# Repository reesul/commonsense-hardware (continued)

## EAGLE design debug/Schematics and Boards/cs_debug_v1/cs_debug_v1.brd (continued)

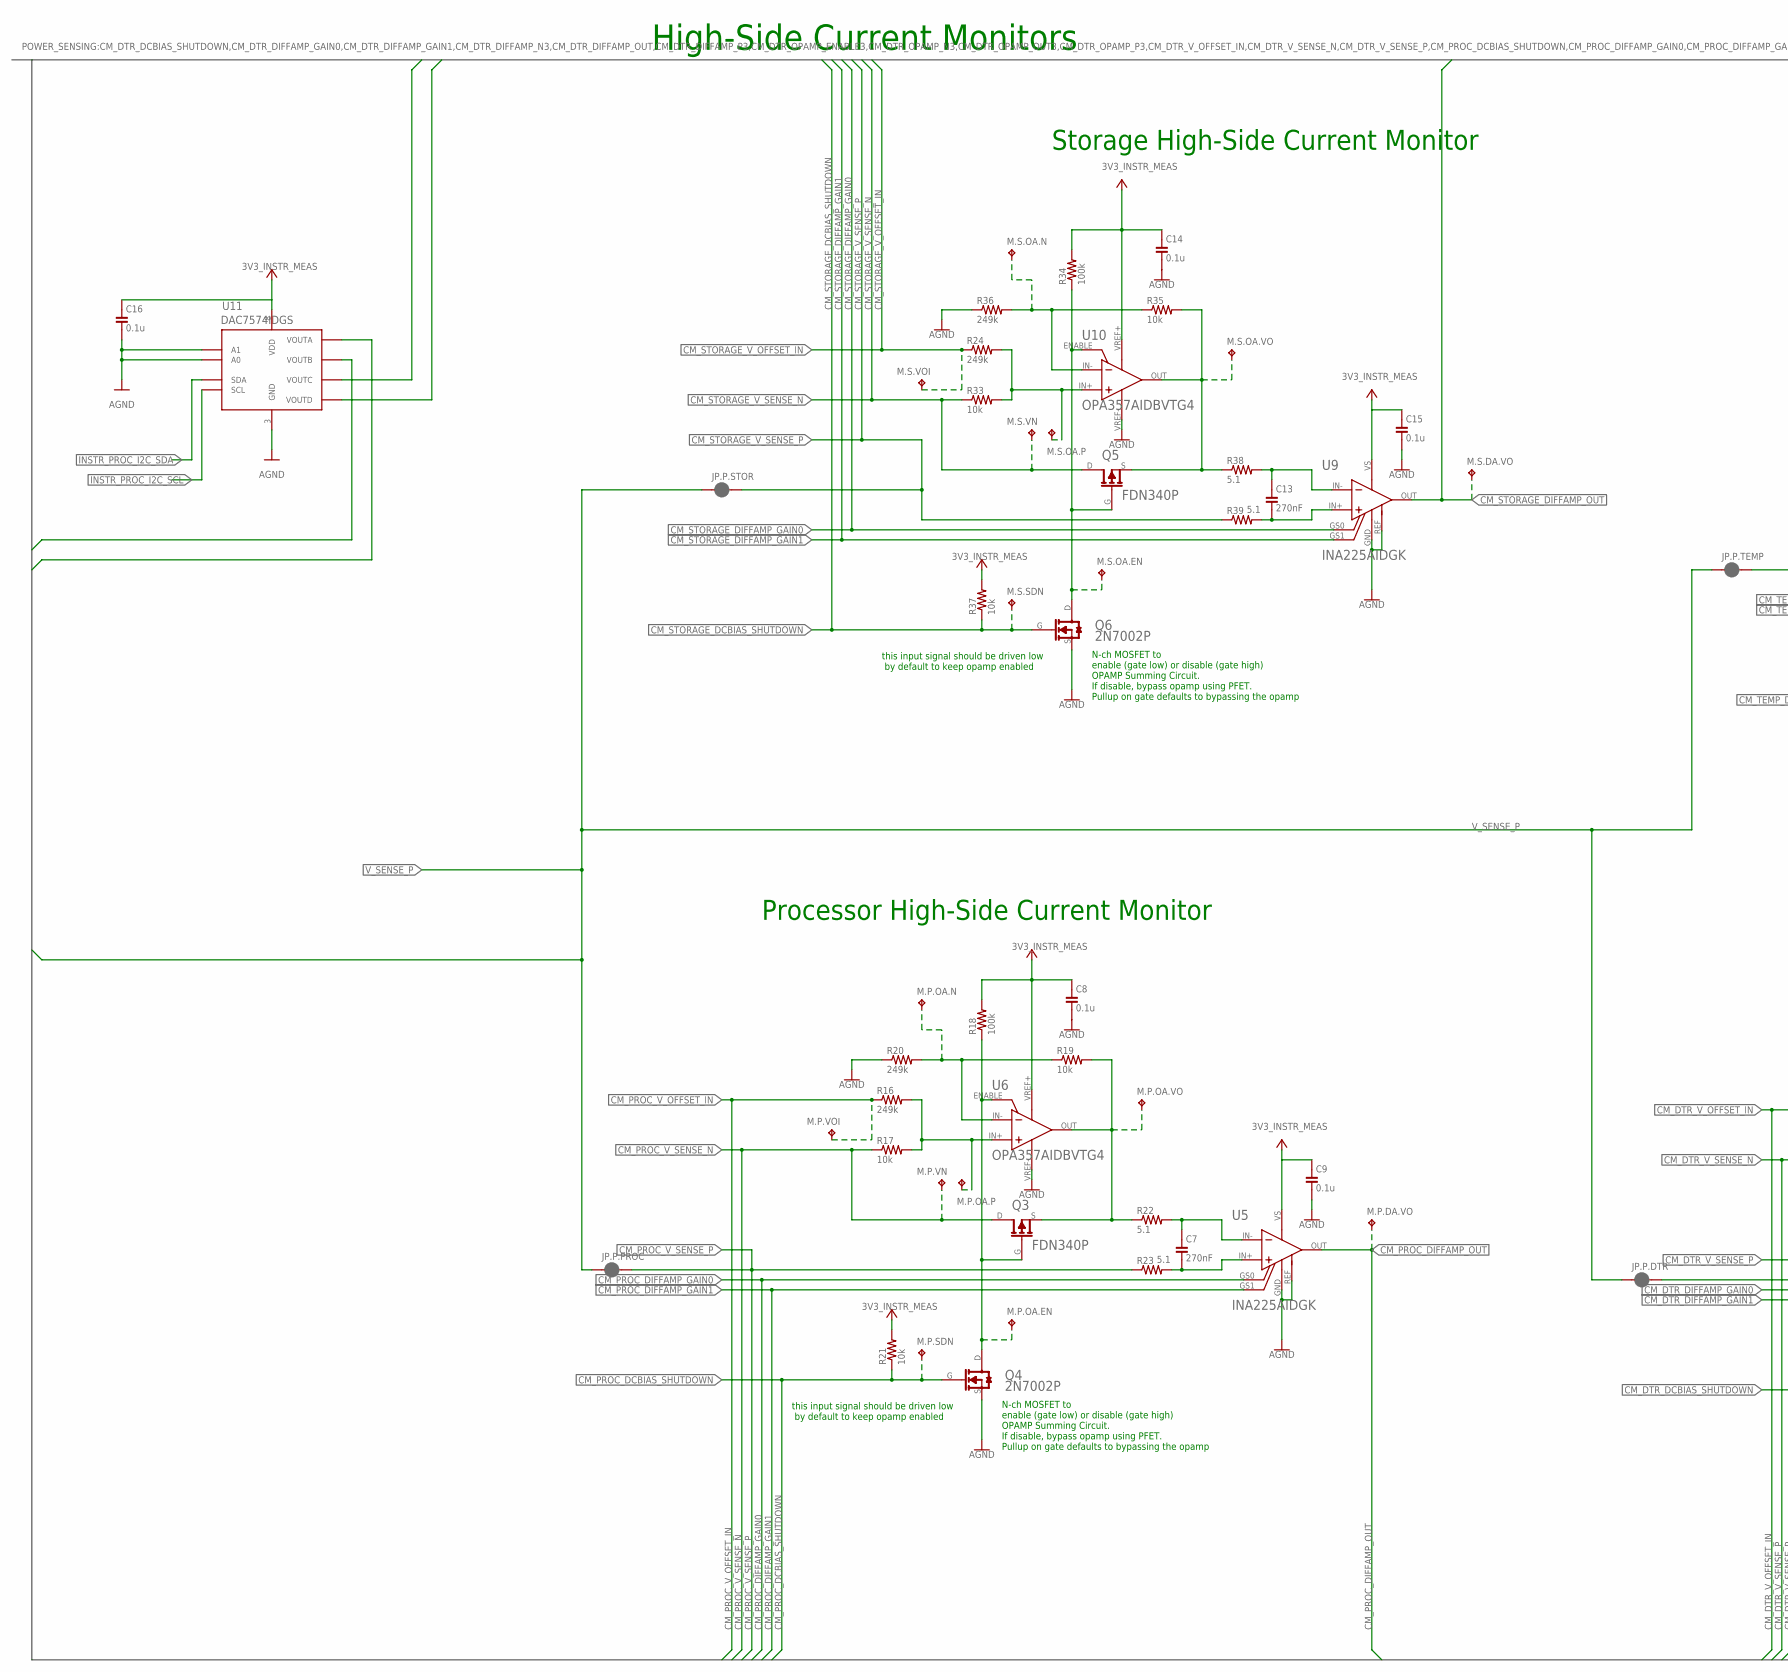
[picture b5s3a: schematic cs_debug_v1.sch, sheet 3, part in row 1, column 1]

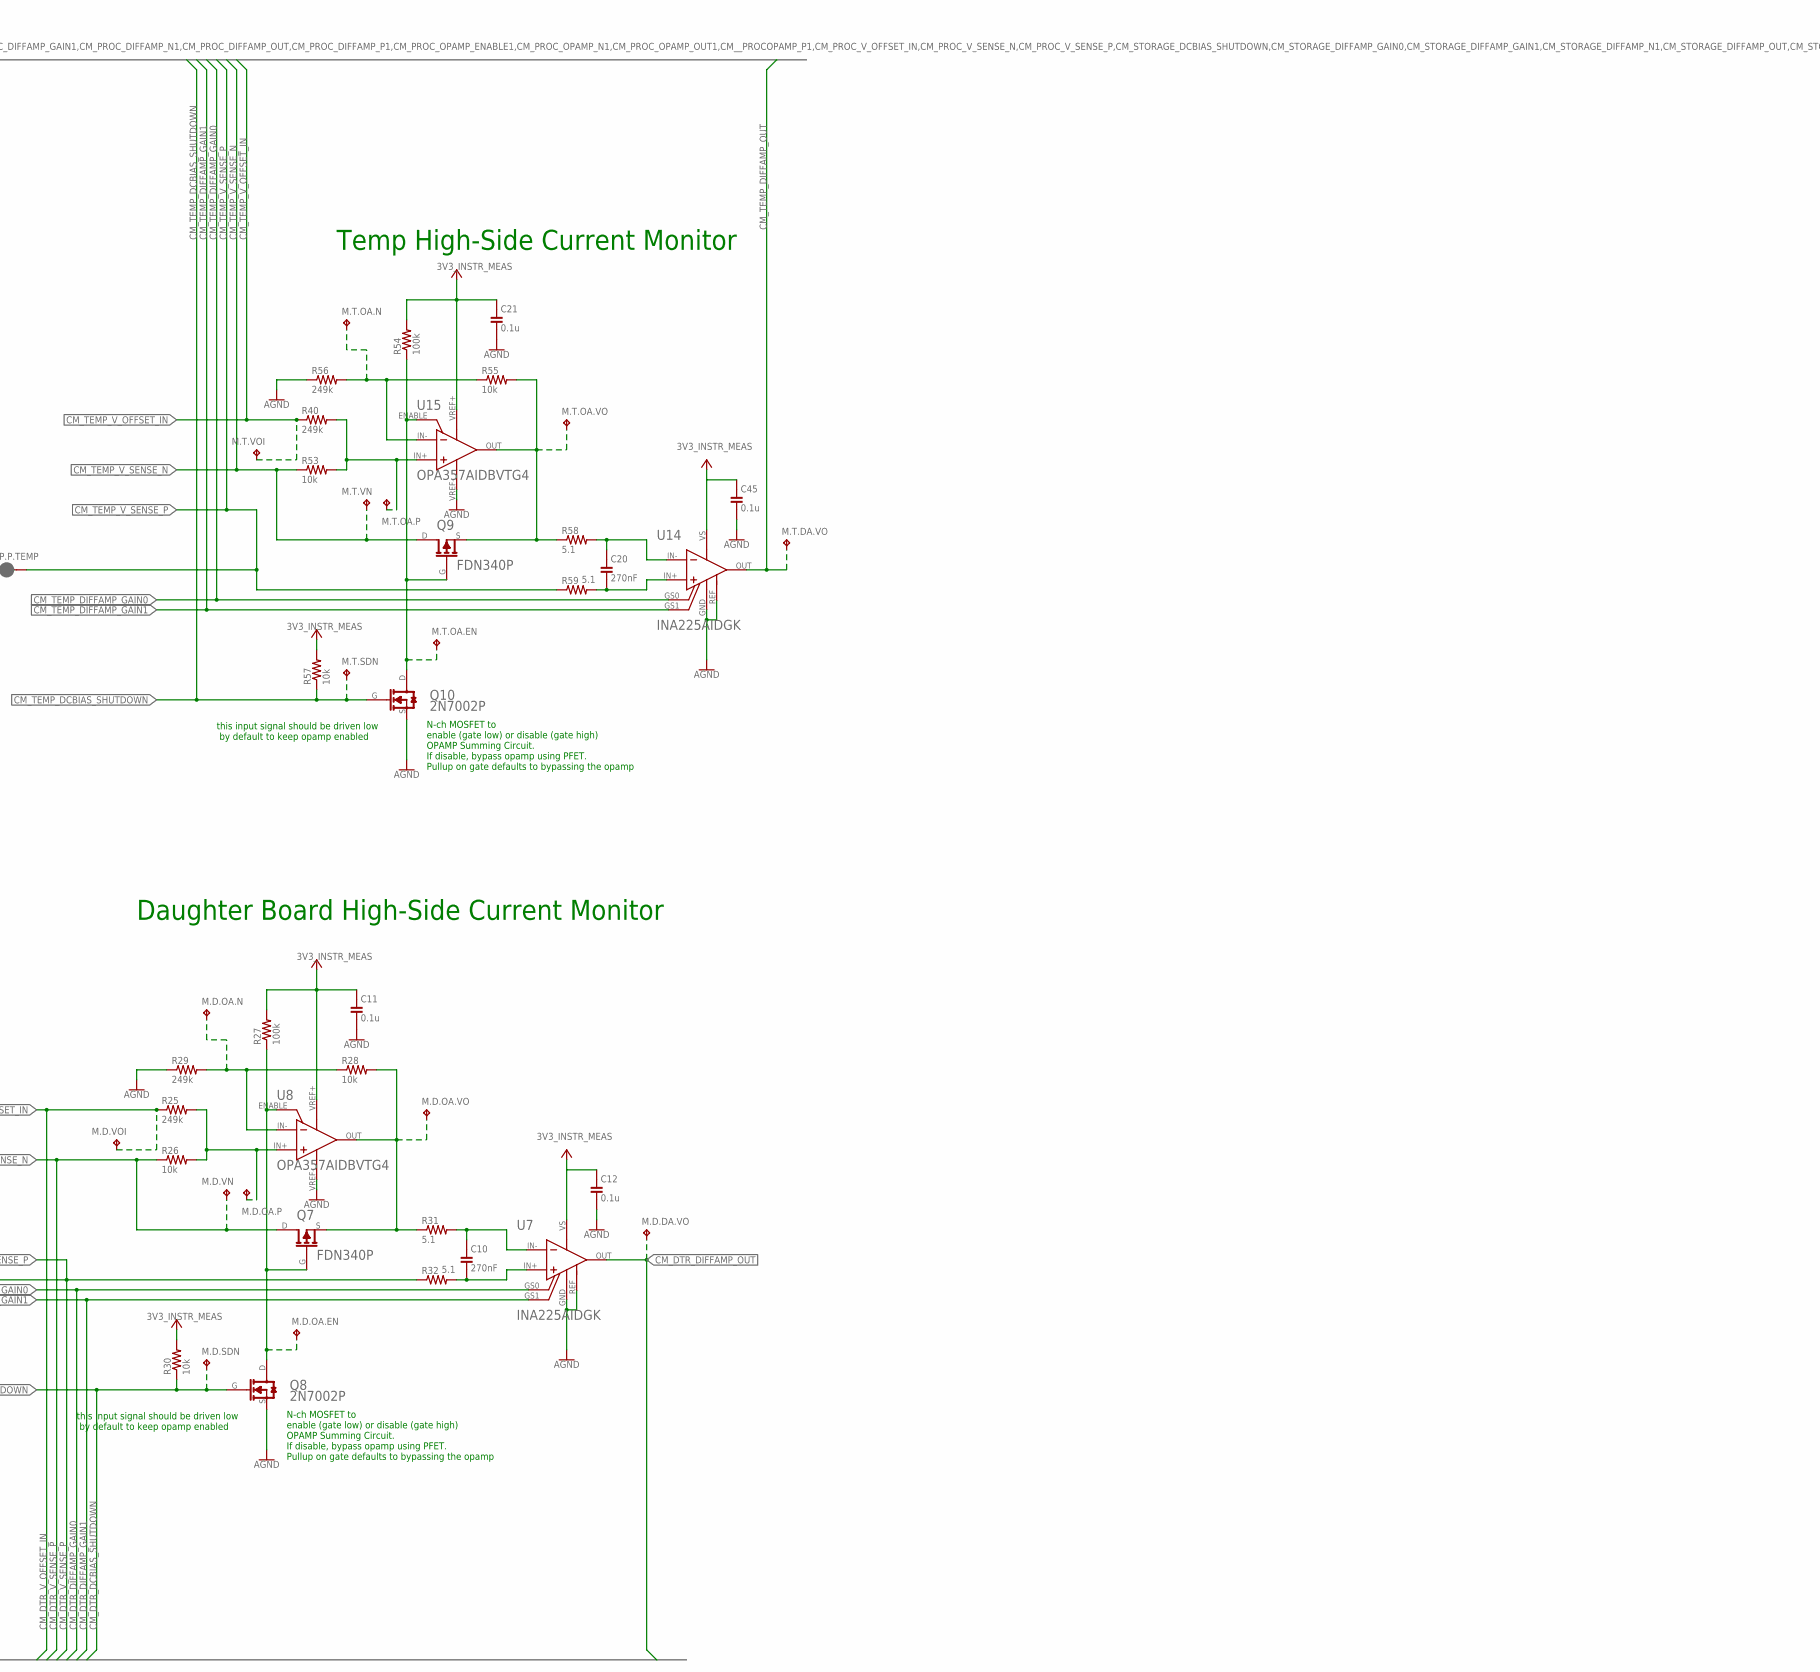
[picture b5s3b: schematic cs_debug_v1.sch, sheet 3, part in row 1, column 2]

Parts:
C7, C10, C13, C20: 270nF; C0603; VOLTAGE 10V; MPN C0603C274K8PACTU
C8, C9, C11, C12, C14, C15, C16, C21, C45: 0.1u; C0402; VOLTAGE 10V; MPN C0402C104K8RACTU
JP.P.DTR, JP.P.PROC, JP.P.STOR, JP.P.TEMP: JUMPER-SMT_2_NC_PASTE_NO-SILK; SMT-JUMPER_2_NC_PASTE_NO-SILK
M.D.DA.VO, M.D.OA.EN, M.D.OA.N, M.D.OA.P, M.D.OA.VO, M.D.SDN, M.D.VN, M.D.VOI, M.P.DA.VO, M.P.OA.EN, M.P.OA.N, M.P.OA.P, M.P.OA.VO, M.P.SDN, M.P.VN, M.P.VOI, M.S.DA.VO, M.S.OA.EN, M.S.OA.N, M.S.OA.P, M.S.OA.VO, M.S.SDN, M.S.VN, M.S.VOI, M.T.DA.VO, M.T.OA.EN, M.T.OA.N, M.T.OA.P, M.T.OA.VO, M.T.SDN, M.T.VN, M.T.VOI: TPTP10SQ; TP10SQ
Q3, Q5, Q7, Q9: FDN340P; SOT23-3_FDN340P; PART_NO FDN340P
Q4, Q6, Q8, Q10: 2N7002P; SOT23-3_2N7002P; PART_NO 2N7002P
R16, R20, R24, R25, R29, R36, R40, R56: 249k; R0402; MPN ERA-2AEB2491X
R17, R19, R26, R28, R33, R35, R53, R55: 10k; R0402; MPN ERA-2AEB103X
R18, R27, R34, R54: 100k; R0402; MPN ERJ-2RKF1003X
R21, R30, R37, R57: 10k; R0402; MPN ERJ-2RKF1002X
R22, R23, R31, R32, R38, R39, R58, R59: 5.1; R0603; MPN ERJ-3BQF5R1V
U5, U7, U9, U14: INA225AIDGK; DGK-MSOP8_INA225; MPN INA225AIDGKT
U6, U8, U10, U15: OPA357AIDBVTG4; PART_NO OPA357AIDBVTG4
U11: DAC7574IDGS; DGS10; MPN DAC7574IDGS

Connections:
3V3_INSTR_MEAS: C8.1, C9.1, C11.1, C12.1, C14.1, C15.1, C16.1, C21.1, C45.1, R18.2, R21.2, R27.2, R30.2, R34.2, R37.2, R54.2, R57.2, U5.VS (V+), U6.VREF+ (V+), U7.VS (V+), U8.VREF+ (V+), U9.VS (V+), U10.VREF+ (V+), U11.8 (VDD), U14.VS (V+), U15.VREF+ (V+); also elsewhere on the board
AGND: C8.2, C9.2, C11.2, C12.2, C14.2, C15.2, C16.2, C21.2, C45.2, Q4.S (SOURCE), Q6.S (SOURCE), Q8.S (SOURCE), Q10.S (SOURCE), R20.1, R29.1, R36.1, R56.1, U5.GND (V-), U5.REF, U6.VREF- (V-), U7.GND (V-), U7.REF, U8.VREF- (V-), U9.GND (V-), U9.REF, U10.VREF- (V-), U11.3 (GND), U11.9 (A0), U11.10 (A1), U14.GND (V-), U14.REF, U15.VREF- (V-); also elsewhere on the board
CM_DIFFAMP_N1: C20.1, R58.2, U14.IN-
CM_DIFFAMP_N2: C13.1, R38.2, U9.IN-
CM_DIFFAMP_N3: C10.1, R31.2, U7.IN-
CM_DIFFAMP_N4: C7.1, R22.2, U5.IN-
CM_DIFFAMP_P1: C20.2, R59.2, U14.IN+
CM_DIFFAMP_P2: C13.2, R39.2, U9.IN+
CM_DIFFAMP_P3: C10.2, R32.2, U7.IN+
CM_DIFFAMP_P4: C7.2, R23.2, U5.IN+
CM_DTR_DCBIAS_SHUTDOWN: M.D.SDN.TP, Q8.G (GATE), R30.1; also elsewhere on the board
CM_DTR_DIFFAMP_GAIN0: U7.GS0; also elsewhere on the board
CM_DTR_DIFFAMP_GAIN1: U7.GS1; also elsewhere on the board
CM_DTR_DIFFAMP_OUT: M.D.DA.VO.TP, U7.OUT; also elsewhere on the board
CM_DTR_V_OFFSET_IN: M.D.VOI.TP, R25.1, U11.2 (VOUTB)
CM_DTR_V_SENSE_N: M.D.VN.TP, Q7.D, R26.1; also elsewhere on the board
CM_DTR_V_SENSE_P: JP.P.DTR.2, R32.1
CM_OPAMP_ENABLE1: M.T.OA.EN.TP, Q9.G, Q10.D (DRAIN), R54.1, U15.ENABLE
CM_OPAMP_ENABLE2: M.S.OA.EN.TP, Q5.G, Q6.D (DRAIN), R34.1, U10.ENABLE
CM_OPAMP_ENABLE3: M.D.OA.EN.TP, Q7.G, Q8.D (DRAIN), R27.1, U8.ENABLE
CM_OPAMP_ENABLE4: M.P.OA.EN.TP, Q3.G, Q4.D (DRAIN), R18.1, U6.ENABLE
CM_OPAMP_N1: M.T.OA.N.TP, R55.1, R56.2, U15.IN-
CM_OPAMP_N2: M.S.OA.N.TP, R35.1, R36.2, U10.IN-
CM_OPAMP_N3: M.D.OA.N.TP, R28.1, R29.2, U8.IN-
CM_OPAMP_N4: M.P.OA.N.TP, R19.1, R20.2, U6.IN-
CM_OPAMP_OUT1: M.T.OA.VO.TP, Q9.S, R55.2, R58.1, U15.OUT
CM_OPAMP_OUT2: M.S.OA.VO.TP, Q5.S, R35.2, R38.1, U10.OUT
CM_OPAMP_OUT3: M.D.OA.VO.TP, Q7.S, R28.2, R31.1, U8.OUT
CM_OPAMP_OUT4: M.P.OA.VO.TP, Q3.S, R19.2, R22.1, U6.OUT
CM_OPAMP_P1: M.T.OA.P.TP, R40.2, R53.2, U15.IN+
CM_OPAMP_P2: M.S.OA.P.TP, R24.2, R33.2, U10.IN+
CM_OPAMP_P3: M.D.OA.P.TP, R25.2, R26.2, U8.IN+
CM_OPAMP_P4: M.P.OA.P.TP, R16.2, R17.2, U6.IN+
CM_PROC_DCBIAS_SHUTDOWN: M.P.SDN.TP, Q4.G (GATE), R21.1; also elsewhere on the board
CM_PROC_DIFFAMP_GAIN0: U5.GS0; also elsewhere on the board
CM_PROC_DIFFAMP_GAIN1: U5.GS1; also elsewhere on the board
CM_PROC_DIFFAMP_OUT: M.P.DA.VO.TP, U5.OUT; also elsewhere on the board
CM_PROC_V_OFFSET_IN: M.P.VOI.TP, R16.1, U11.1 (VOUTA)
CM_PROC_V_SENSE_N: M.P.VN.TP, Q3.D, R17.1; also elsewhere on the board
CM_PROC_V_SENSE_P: JP.P.PROC.2, R23.1
CM_STORAGE_DCBIAS_SHUTDOWN: M.S.SDN.TP, Q6.G (GATE), R37.1; also elsewhere on the board
CM_STORAGE_DIFFAMP_GAIN0: U9.GS0; also elsewhere on the board
CM_STORAGE_DIFFAMP_GAIN1: U9.GS1; also elsewhere on the board
CM_STORAGE_DIFFAMP_OUT: M.S.DA.VO.TP, U9.OUT; also elsewhere on the board
CM_STORAGE_V_OFFSET_IN: M.S.VOI.TP, R24.1, U11.4 (VOUTC)
CM_STORAGE_V_SENSE_N: M.S.VN.TP, Q5.D, R33.1; also elsewhere on the board
CM_STORAGE_V_SENSE_P: JP.P.STOR.2, R39.1
CM_TEMP_DCBIAS_SHUTDOWN: M.T.SDN.TP, Q10.G (GATE), R57.1; also elsewhere on the board
CM_TEMP_DIFFAMP_GAIN0: U14.GS0; also elsewhere on the board
CM_TEMP_DIFFAMP_GAIN1: U14.GS1; also elsewhere on the board
CM_TEMP_DIFFAMP_OUT: M.T.DA.VO.TP, U14.OUT; also elsewhere on the board
CM_TEMP_V_OFFSET_IN: M.T.VOI.TP, R40.1, U11.5 (VOUTD)
CM_TEMP_V_SENSE_N: M.T.VN.TP, Q9.D, R53.1; also elsewhere on the board
CM_TEMP_V_SENSE_P: JP.P.TEMP.2, R59.1
INSTR_PROC_I2C_SCL: U11.6 (SCL); also elsewhere on the board
INSTR_PROC_I2C_SDA: U11.7 (SDA); also elsewhere on the board
V_SENSE_P: JP.P.DTR.1, JP.P.PROC.1, JP.P.STOR.1, JP.P.TEMP.1; also elsewhere on the board

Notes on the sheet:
High-Side Current Monitors
Temp High-Side Current Monitor
this input signal should be driven low by default to keep opamp enabled
N-ch MOSFET to enable (gate low) or disable (gate high) OPAMP Summing Circuit. If disable, bypass opamp using PFET. Pullup on gate defaults to bypassing the opamp
Storage High-Side Current Monitor
Daughter Board High-Side Current Monitor
Processor High-Side Current Monitor

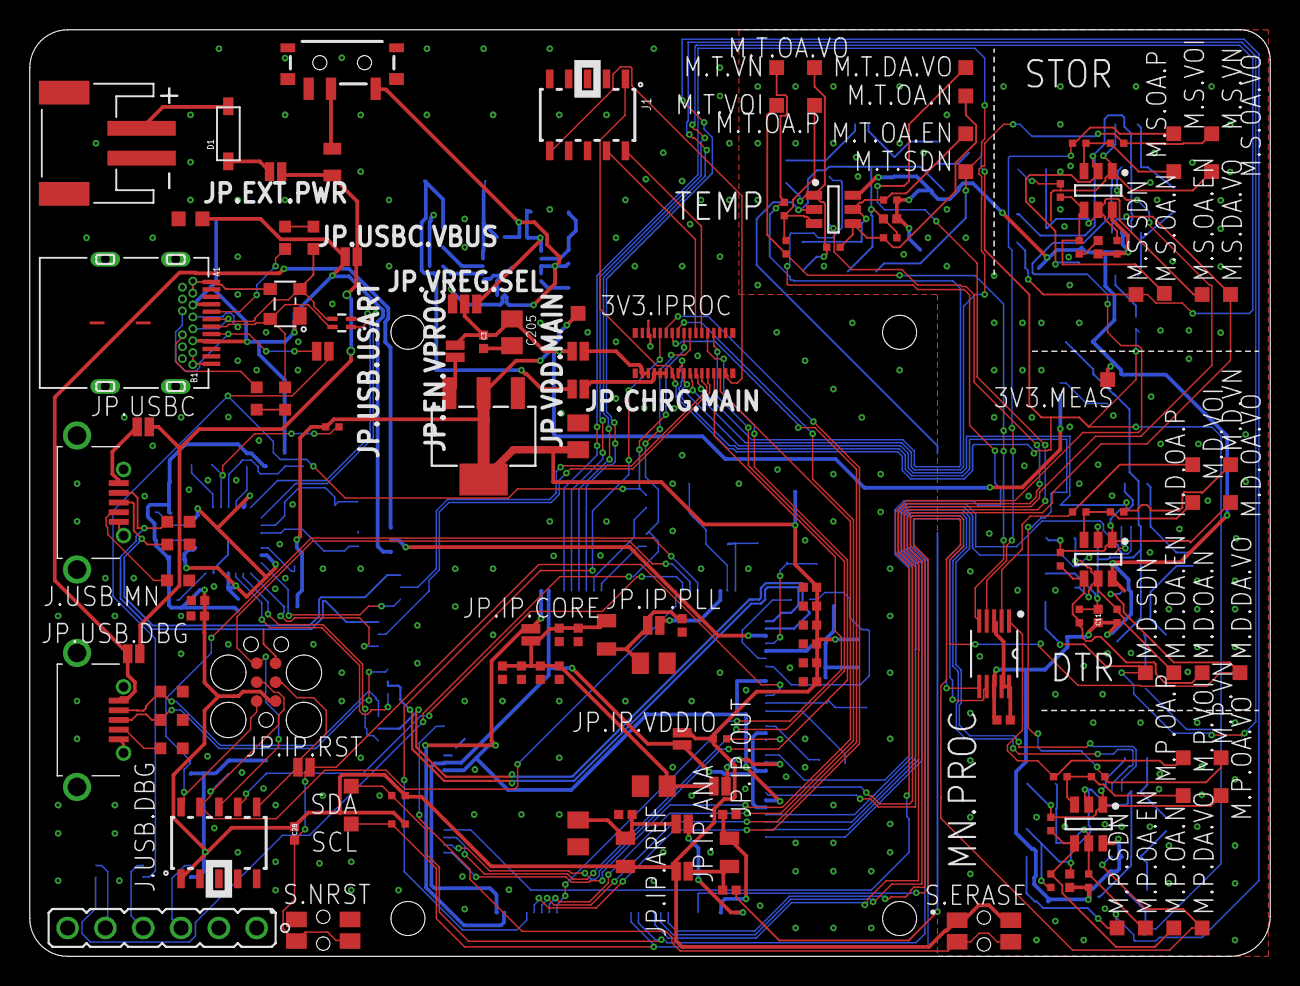
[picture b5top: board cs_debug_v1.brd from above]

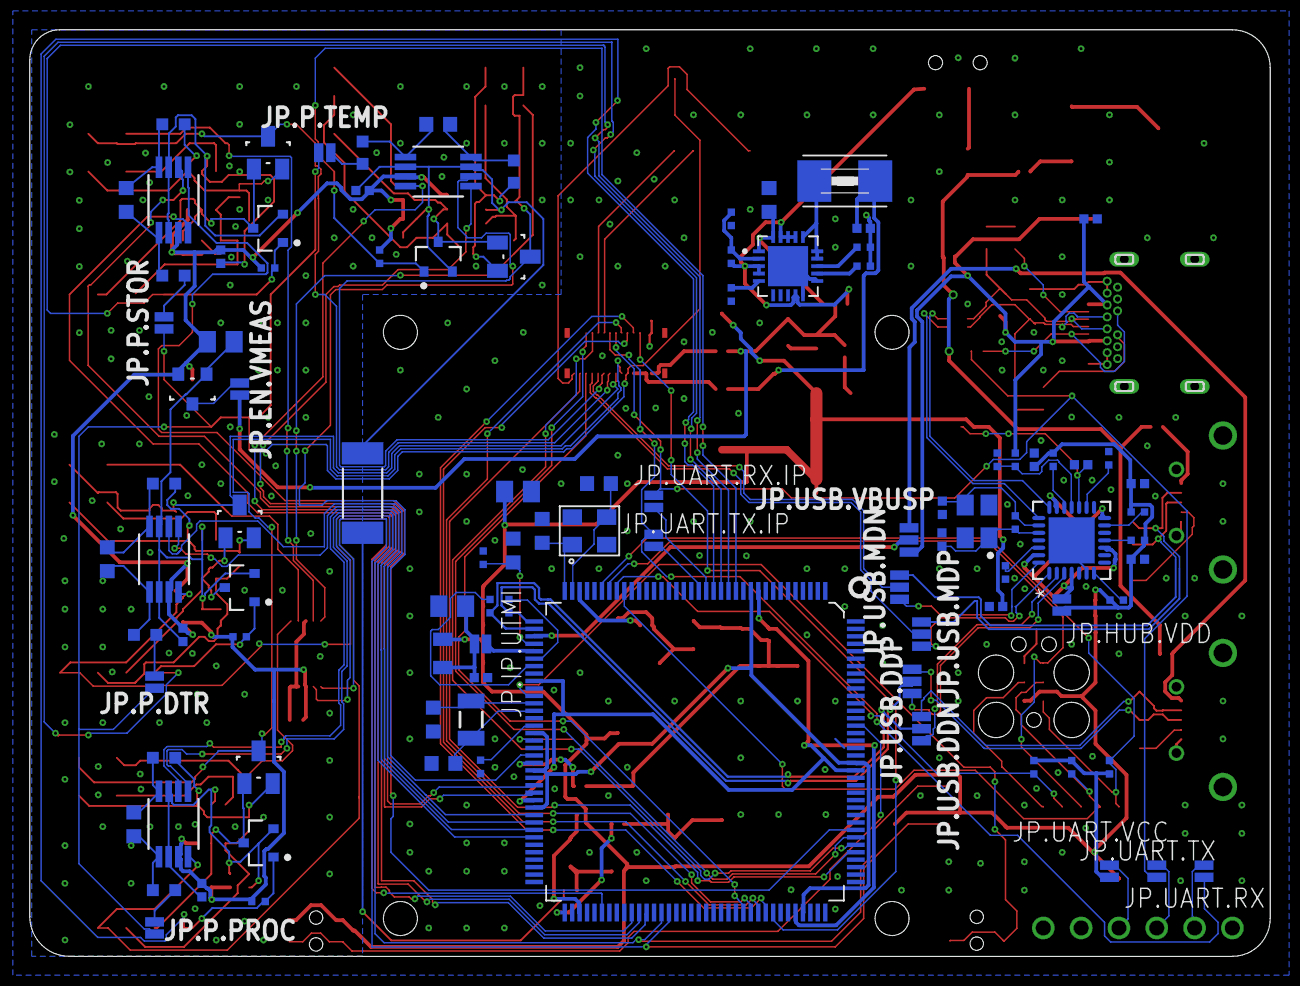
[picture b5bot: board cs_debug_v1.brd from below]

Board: 2 copper layers, 83.2 x 62.1 mm, 241 parts (99 on the bottom side), 158 nets.

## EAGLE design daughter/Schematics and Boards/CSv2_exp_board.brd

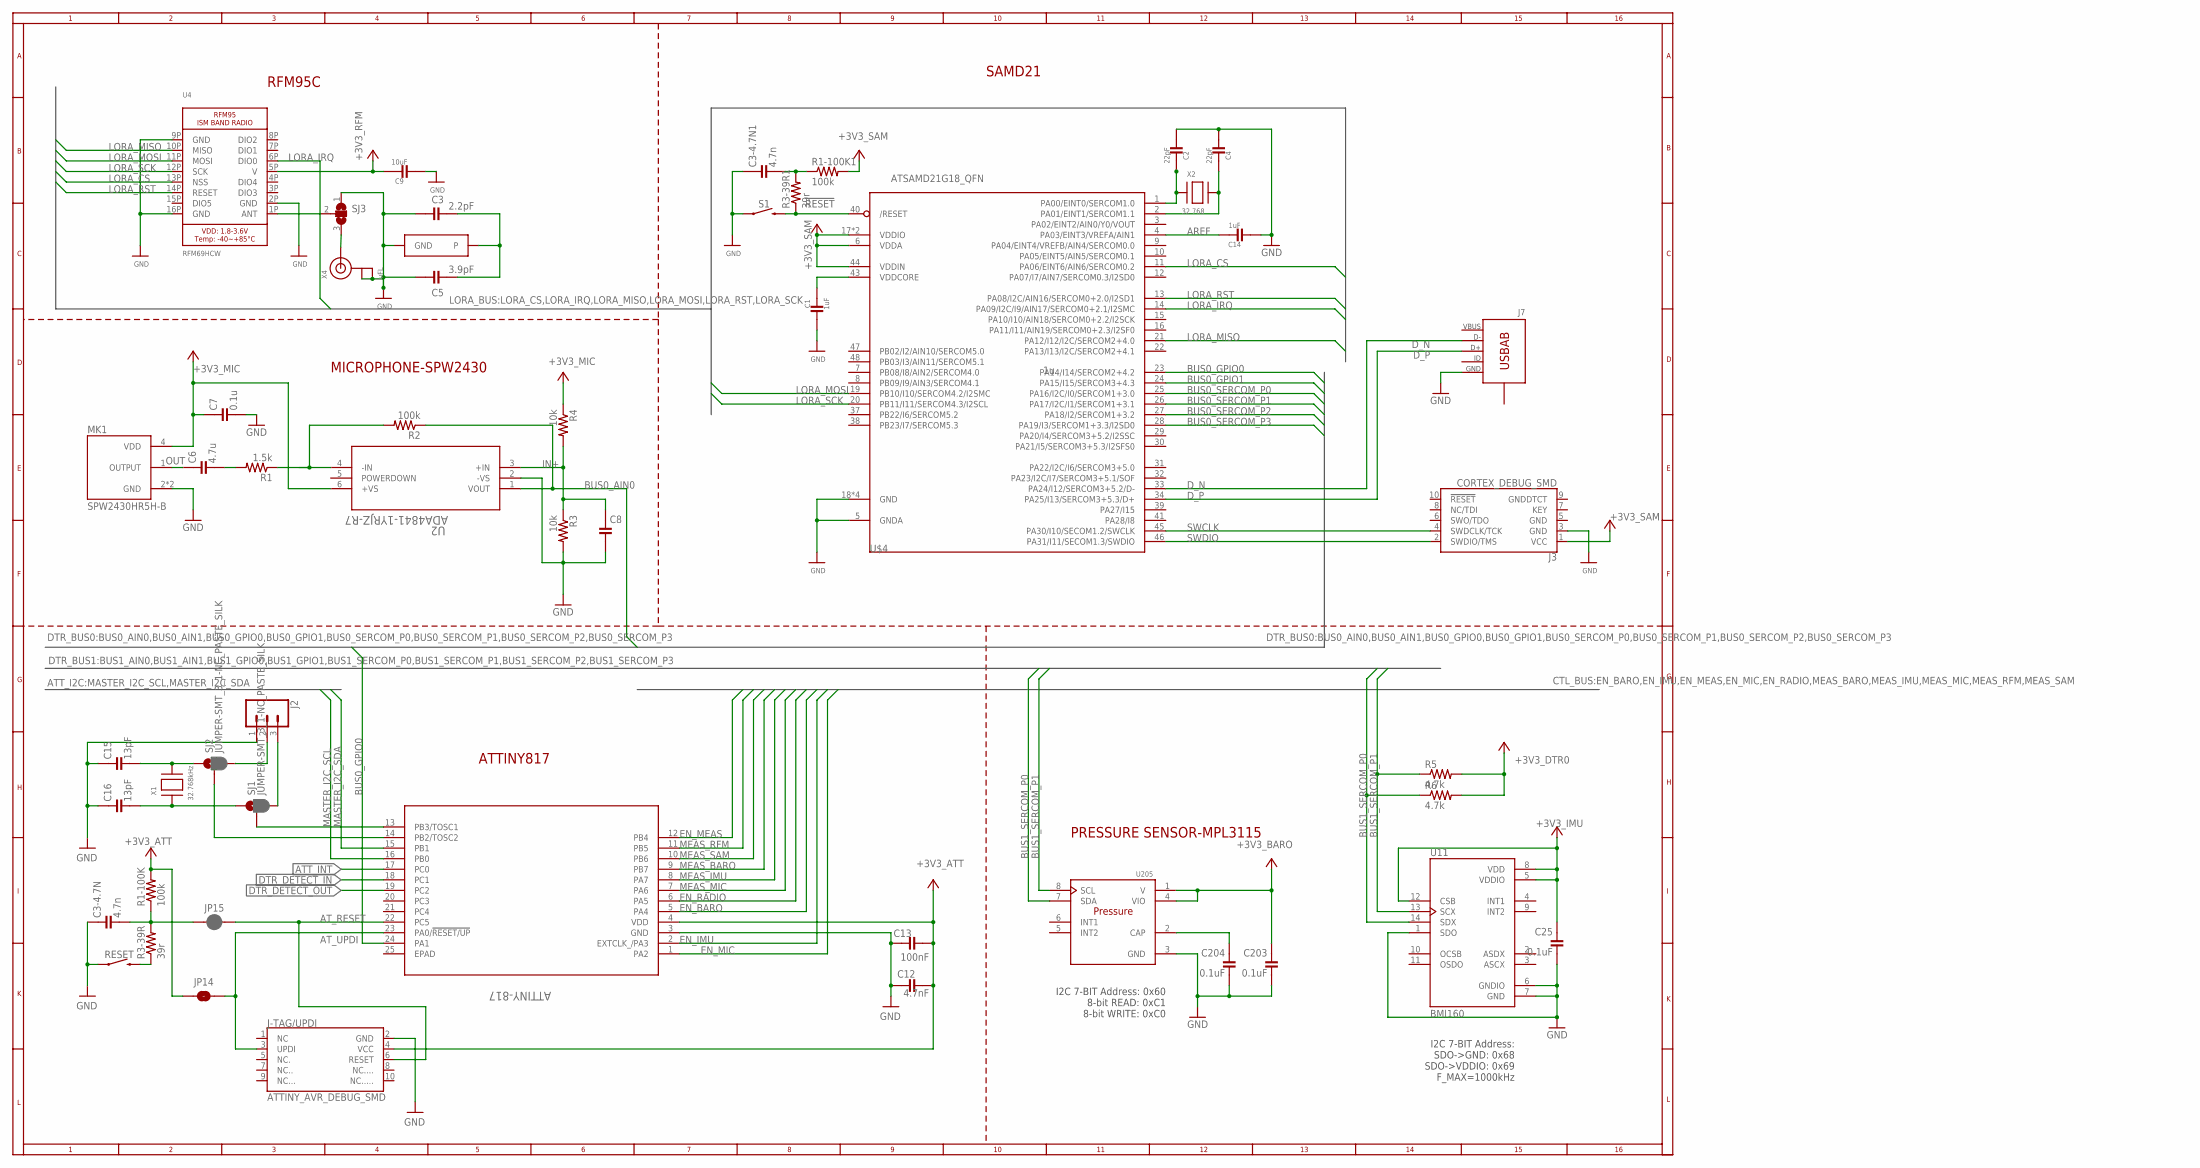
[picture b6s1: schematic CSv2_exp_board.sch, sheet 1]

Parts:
ATTINY-817: ATTINY817-MFRQFN24_RX4MC-L_ATTINY817-MFR; ATTINY817-MFRQFN24_RX4MC-L_QFN24_4X4MC
C1, C14: 1uF; C0603
C2, C4: 22pF; C0603
C3: 2.2pF; C0402
C3-4.7N, C3-4.7N1: 4.7n; C0603
C5: 3.9pF; C0402
C6: 4.7u; C0603
C7: 0.1u; C0603
C8: 1u; C0603
C9: 10uF; C0805
C12: 4.7nF; C0603; PARTNO CC0402KRX5R5BB105
C13: 100nF; C0402; PARTNO CC0402KRX5R5BB105
C15, C16: 13pF; C0402
C25, C203, C204: 0.1uF; C0603
J2: J-SCR-3SL; SCR-3.5MM-3
J3: CORTEX_DEBUG_SMD; SAMTECH_FTSH-105-01
J7: J-USB-HIROSE-MICRO-USB; USB-THRU-ZX62D-AB-5P8
J-TAG/UPDI: ATTINY_AVR_DEBUG_SMD; ATTINY_AVR_DEBUG
JP14: JUMPER-SMT_2_NO_PASTEFREE; SMT-JUMPER_2_NO_PASTEFREE_NO-SILK
JP15: JUMPER-SMT_2_NC_PASTE; SMT-JUMPER_2_LG_NC_PASTE_NO-SILK
MK1: SPW2430HR5H-B; MIC_SPW2430HR5H-B
R1: 1.5k; R0603
R1-100K, R1-100K1: 100k; R0603
R2: 100k; R0603; MPN 3549S-1AA-102A
R3, R4: 10k; R0603
R3-39R, R3-39R1: 39r; R0603
R5, R6: 4.7k; R0805
RESET: MOMENTARY-SWITCH-SPST-SMD-5.2MM; TACTILE_SWITCH_SMD_5.2MM
S1: MOMENTARY-SWITCH-SPST-SMD-5.2MM; TACTILE_SWITCH_SMD_5.2MM
SJ1, SJ2: JUMPER-SMT_3_1-NC_PASTE_SILK; SMT-JUMPER_3_1-NC_PASTE_SILK
SJ3: JUMPER_SJ2W; JUMPER_SJ_2
U2: ADA4841-1YRJZ-R7; RJ_6
U4: RFM69HCW; RFM-MOD
U11: BMI160; PQFN50P300X250X88-14N
U205: MPL3115A2; MPL3115A2_PSON125P300X500X120-8N
U$1: ILA09_CHIP_ANTENNASMD; ILA_09_CHIP_ANTENNA
U$4: ATSAMD21G18_QFN; MICROBUILDER_TQFN48_7MM
X1: 32.768kHz; ADAFRUIT2_XTAL3215
X2: 32.768; ADAFRUIT2_XTAL3215
X4: uFL; U.FL

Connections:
!RESET: R3-39R1.1, S1.3 (2), U$4.40 (/RESET)
+3V3_ATT: ATTINY-817.4 (VDD), C12.2, C13.2, J-TAG/UPDI.4 (VCC), JP14.1, R1-100K.2; also elsewhere on the board
+3V3_BARO: C203.1, U205.1 (V), U205.4 (VIO); also elsewhere on the board
+3V3_DTR0: R5.2, R6.2; also elsewhere on the board
+3V3_IMU: C25.1, U11.5 (VDDIO), U11.8 (VDD), U11.12 (CSB); also elsewhere on the board
+3V3_MIC: C7.1, MK1.4 (VDD), R4.1, U2.6 (+VS); also elsewhere on the board
+3V3_RFM: C9.1, U4.5P (V); also elsewhere on the board
+3V3_SAM: J3.1 (VCC), R1-100K1.2, U$4.6 (VDDA), U$4.17 (VDDIO), U$4.36 (VDDIO), U$4.44 (VDDIN); also elsewhere on the board
AREF: C14.1, U$4.4 (PA03/EINT3/VREFA/AIN1)
ATT_INT: ATTINY-817.17 (PC0); also elsewhere on the board
AT_RESET: ATTINY-817.22 (PC5), J-TAG/UPDI.6 (RESET), JP15.2
AT_UPDI: ATTINY-817.23 (PA0/!RESET/UP), J-TAG/UPDI.3 (UPDI), JP14.2
BUS0_AIN0: R2.1, U2.1 (VOUT); also elsewhere on the board
BUS0_GPIO0: ATTINY-817.24 (PA1), U$4.23 (PA14/I14/SERCOM2+4.2); also elsewhere on the board
BUS0_GPIO1: U$4.24 (PA15/I15/SERCOM3+4.3); also elsewhere on the board
BUS0_SERCOM_P0: U$4.25 (PA16/I2C/I0/SERCOM1+3.0); also elsewhere on the board
BUS0_SERCOM_P1: U$4.26 (PA17/I2C/I1/SERCOM1+3.1); also elsewhere on the board
BUS0_SERCOM_P2: U$4.27 (PA18/I2/SERCOM1+3.2); also elsewhere on the board
BUS0_SERCOM_P3: U$4.28 (PA19/I3/SERCOM1+3.3/I2SD0); also elsewhere on the board
BUS1_SERCOM_P0: R6.1, U11.14 (SDX), U205.7 (SDA); also elsewhere on the board
BUS1_SERCOM_P1: R5.1, U11.13 (SCX), U205.8 (SCL); also elsewhere on the board
DTR_DETECT_IN: ATTINY-817.18 (PC1); also elsewhere on the board
DTR_DETECT_OUT: ATTINY-817.19 (PC2); also elsewhere on the board
D_N: J7.D-, U$4.33 (PA24/I12/SERCOM3+5.2/D-)
D_P: J7.D+, U$4.34 (PA25/I13/SERCOM3+5.3/D+)
EN_BARO: ATTINY-817.5 (PA4); also elsewhere on the board
EN_IMU: ATTINY-817.2 (EXTCLK_/PA3); also elsewhere on the board
EN_MEAS: ATTINY-817.12 (PB4); also elsewhere on the board
EN_MIC: ATTINY-817.1 (PA2); also elsewhere on the board
EN_RADIO: ATTINY-817.6 (PA5); also elsewhere on the board
GND: ATTINY-817.3 (GND), C1.2, C2.2, C3.1, C3-4.7N.1, C3-4.7N1.1, C4.2, C5.1, C7.2, C8.2, C9.2, C12.1, C13.1, C14.2, C15.1, C16.1, C25.2, C203.2, C204.2, J2.1, J3.3 (GND), J7.GND, J-TAG/UPDI.2 (GND), MK1.2 (GND), MK1.3 (GND), R3.2, RESET.1, S1.1, SJ3.1, U2.2 (-VS), U4.2P (GND), U4.9P (GND), U4.16P (GND), U11.1 (SDO), U11.6 (GNDIO), U11.7 (GND), U205.3 (GND), U$1.GND, U$4.5 (GNDA), U$4.18 (GND), U$4.35 (GND), U$4.42 (GND), U$4.THERMAL (GND), X4.1 (GND), X4.2 (GND); also elsewhere on the board
IN+: C8.1, R3.1, R4.2, U2.3 (+IN)
IN-: R1.1, R2.2, U2.4 (-IN)
LORA_CS: U4.13P (NSS), U$4.11 (PA06/EINT6/AIN6/SERCOM0.2)
LORA_IRQ: U4.6P (DIO0), U$4.14 (PA09/I2C/I9/AIN17/SERCOM0+2.1/I2SMC)
LORA_MISO: U4.10P (MISO), U$4.21 (PA12/I12/I2C/SERCOM2+4.0)
LORA_MOSI: U4.11P (MOSI), U$4.19 (PB10/I10/SERCOM4.2/I2SMC)
LORA_RST: U4.14P (RESET), U$4.13 (PA08/I2C/AIN16/SERCOM0+2.0/I2SD1)
LORA_SCK: U4.12P (SCK), U$4.20 (PB11/I11/SERCOM4.3/I2SCL)
MASTER_I2C_SCL: ATTINY-817.16 (PB0); also elsewhere on the board
MASTER_I2C_SDA: ATTINY-817.15 (PB1); also elsewhere on the board
MEAS_BARO: ATTINY-817.9 (PB7); also elsewhere on the board
MEAS_IMU: ATTINY-817.8 (PA7); also elsewhere on the board
MEAS_MIC: ATTINY-817.7 (PA6); also elsewhere on the board
MEAS_RFM: ATTINY-817.11 (PB5); also elsewhere on the board
MEAS_SAM: ATTINY-817.10 (PB6); also elsewhere on the board
unnamed: C1.1, U$4.43 (VDDCORE)
unnamed: SJ3.3, X4.3 (SIGNAL)
unnamed: C2.1, U$4.1 (PA00/EINT0/SERCOM1.0), X2.P$1
unnamed: C6.2, R1.2
unnamed: C4.1, U$4.2 (PA01/EINT1/SERCOM1.1), X2.P$2
unnamed: C3-4.7N1.2, R1-100K1.1, R3-39R1.2
unnamed: C204.1, U205.2 (CAP)
unnamed: R3-39R.1, RESET.3 (2)
unnamed: ATTINY-817.13 (PB3/TOSC1), SJ1.2
unnamed: ATTINY-817.14 (PB2/TOSC2), SJ2.2
unnamed: J2.2, SJ2.3
unnamed: J2.3, SJ1.3
unnamed: C16.2, SJ1.1, X1.P$1
unnamed: C15.2, SJ2.1, X1.P$2
unnamed: C3-4.7N.2, JP15.1, R1-100K.1, R3-39R.2
unnamed: C3.2, C5.2, U$1.P
unnamed: SJ3.2, U4.1P (ANT)
OUT: C6.1, MK1.1 (OUTPUT)
POWERDOWN: U2.5 (POWERDOWN)
SWCLK: J3.4 (SWDCLK/TCK), U$4.45 (PA30/I10/SECOM1.2/SWCLK)
SWDIO: J3.2 (SWDIO/TMS), U$4.46 (PA31/I11/SECOM1.3/SWDIO)

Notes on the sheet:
RFM95C
SAMD21
ATTINY817
MICROPHONE-SPW2430
I2C 7-BIT Address: 0x60 8-bit READ: 0xC1 8-bit WRITE: 0xC0
PRESSURE SENSOR-MPL3115
I2C 7-BIT Address: SDO->GND: 0x68 SDO->VDDIO: 0x69 F_MAX=1000kHz

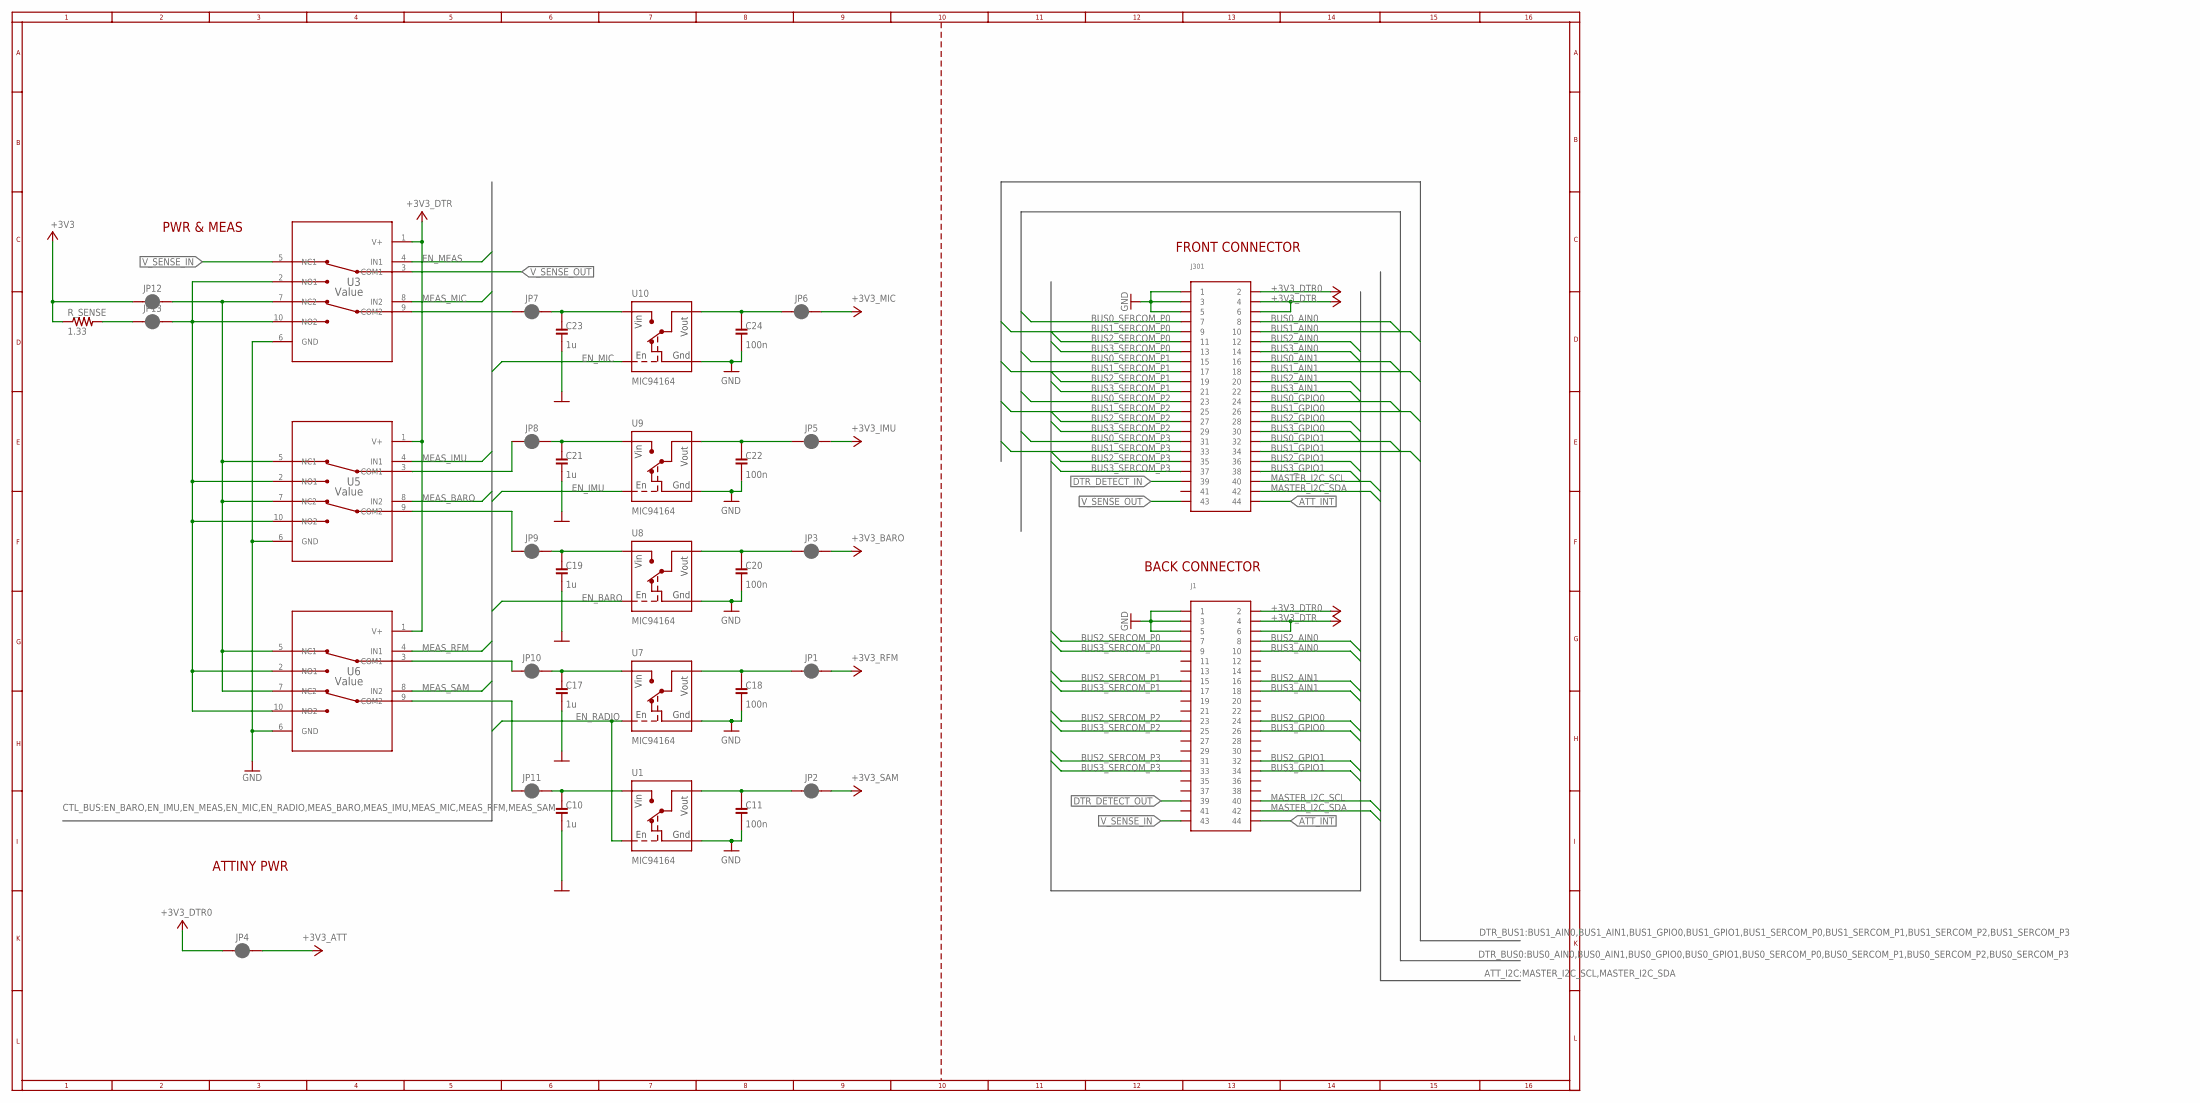
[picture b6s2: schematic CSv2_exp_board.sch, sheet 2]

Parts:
C10, C17, C19, C21, C23: 1u; C0402; PARTNO CC0402KRX5R5BB105
C11, C18, C20, C22, C24: 100n; C0402; PARTNO CC0402KRX5R5BB104
J1, J301: HIROSE-DF40_44-PIN_CONNECTORS-RECEPTACLE; HRS_DF40HC(3.0)-44DS-0.4V(51); PART_NO DF40HC(3.0)-44DS-0.4V(51)
JP1, JP2, JP3, JP4, JP5, JP6, JP7, JP8, JP9, JP10, JP11, JP12, JP13: JUMPER-SMT_2_NC_PASTE; SMT-JUMPER_2_LG_NC_PASTE_NO-SILK
R_SENSE: 1.33; R0603; PARTNO CRCW06031R33FKEA
U1, U7, U8, U9, U10: LOADSWITCH-MIC94164; WLCSP6_2X3
U3, U5, U6: Value; DGS0010A_L

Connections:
3V_LD_SW: C10.1, JP11.2, U1.A2 (VIN), U1.B2 (VIN)
3V_LD_SW1: C17.1, JP10.2, U7.A2 (VIN), U7.B2 (VIN)
3V_LD_SW2: C19.1, JP9.2, U8.A2 (VIN), U8.B2 (VIN)
3V_LD_SW3: C21.1, JP8.2, U9.A2 (VIN), U9.B2 (VIN)
3V_LD_SW4: C23.1, JP7.2, U10.A2 (VIN), U10.B2 (VIN)
+3V3: JP12.1, R_SENSE.1
+3V3_ATT: JP4.2; also elsewhere on the board
+3V3_BARO: JP3.2; also elsewhere on the board
+3V3_DTR: J1.4, J1.6, J301.4, J301.6, U3.1 (V+), U5.1 (V+), U6.1 (V+)
+3V3_DTR0: J1.2, J301.2, JP4.1; also elsewhere on the board
+3V3_IMU: JP5.2; also elsewhere on the board
+3V3_MIC: JP6.2; also elsewhere on the board
+3V3_RFM: JP1.2; also elsewhere on the board
+3V3_SAM: JP2.2; also elsewhere on the board
ATT_INT: J1.44, J301.44; also elsewhere on the board
BUS0_AIN0: J301.8; also elsewhere on the board
BUS0_AIN1: J301.16
BUS0_GPIO0: J301.24; also elsewhere on the board
BUS0_GPIO1: J301.32; also elsewhere on the board
BUS0_SERCOM_P0: J301.7; also elsewhere on the board
BUS0_SERCOM_P1: J301.15; also elsewhere on the board
BUS0_SERCOM_P2: J301.23; also elsewhere on the board
BUS0_SERCOM_P3: J301.31; also elsewhere on the board
BUS1_AIN0: J301.10
BUS1_AIN1: J301.18
BUS1_GPIO0: J301.26
BUS1_GPIO1: J301.34
BUS1_SERCOM_P0: J301.9; also elsewhere on the board
BUS1_SERCOM_P1: J301.17; also elsewhere on the board
BUS1_SERCOM_P2: J301.25
BUS1_SERCOM_P3: J301.33
BUS2_AIN0: J1.8, J301.12
BUS2_AIN1: J1.16, J301.20
BUS2_GPIO0: J1.24, J301.28
BUS2_GPIO1: J1.32, J301.36
BUS2_SERCOM_P0: J1.7, J301.11
BUS2_SERCOM_P1: J1.15, J301.19
BUS2_SERCOM_P2: J1.23, J301.27
BUS2_SERCOM_P3: J1.31, J301.35
BUS3_AIN0: J1.10, J301.14
BUS3_AIN1: J1.18, J301.22
BUS3_GPIO0: J1.26, J301.30
BUS3_GPIO1: J1.34, J301.38
BUS3_SERCOM_P0: J1.9, J301.13
BUS3_SERCOM_P1: J1.17, J301.21
BUS3_SERCOM_P2: J1.25, J301.29
BUS3_SERCOM_P3: J1.33, J301.37
DTR_DETECT_IN: J301.39; also elsewhere on the board
DTR_DETECT_OUT: J1.39; also elsewhere on the board
EN_BARO: U8.C2 (ENABLE); also elsewhere on the board
EN_IMU: U9.C2 (ENABLE); also elsewhere on the board
EN_MEAS: U3.4 (IN1); also elsewhere on the board
EN_MIC: U10.C2 (ENABLE); also elsewhere on the board
EN_RADIO: U1.C2 (ENABLE), U7.C2 (ENABLE); also elsewhere on the board
GND: C10.2, C11.2, C17.2, C18.2, C19.2, C20.2, C21.2, C22.2, C23.2, C24.2, J1.1, J1.3, J1.5, J301.1, J301.3, J301.5, U1.C1 (GND), U3.6 (GND), U5.6 (GND), U6.6 (GND), U7.C1 (GND), U8.C1 (GND), U9.C1 (GND), U10.C1 (GND); also elsewhere on the board
MASTER_I2C_SCL: J1.40, J301.40; also elsewhere on the board
MASTER_I2C_SDA: J1.42, J301.42; also elsewhere on the board
MEAS_BARO: U5.8 (IN2); also elsewhere on the board
MEAS_IMU: U5.4 (IN1); also elsewhere on the board
MEAS_MIC: U3.8 (IN2); also elsewhere on the board
MEAS_RFM: U6.4 (IN1); also elsewhere on the board
MEAS_SAM: U6.8 (IN2); also elsewhere on the board
N0: C11.1, JP2.1, U1.A1 (VOUT), U1.B1 (VOUT)
N1: C18.1, JP1.1, U7.A1 (VOUT), U7.B1 (VOUT)
N2: C20.1, JP3.1, U8.A1 (VOUT), U8.B1 (VOUT)
N3: C22.1, JP5.1, U9.A1 (VOUT), U9.B1 (VOUT)
N4: C24.1, JP6.1, U10.A1 (VOUT), U10.B1 (VOUT)
unnamed: JP7.1, U3.9 (COM2)
unnamed: JP13.2, U3.2 (NO1), U3.10 (NO2), U5.2 (NO1), U5.10 (NO2), U6.2 (NO1), U6.10 (NO2)
unnamed: JP13.1, R_SENSE.2
unnamed: JP8.1, U5.3 (COM1)
unnamed: JP9.1, U5.9 (COM2)
unnamed: JP10.1, U6.3 (COM1)
unnamed: JP11.1, U6.9 (COM2)
unnamed: JP12.2, U3.7 (NC2), U5.5 (NC1), U5.7 (NC2), U6.5 (NC1), U6.7 (NC2)
V_SENSE_IN: J1.43, U3.5 (NC1)
V_SENSE_OUT: J301.43, U3.3 (COM1)

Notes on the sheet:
PWR & MEAS
ATTINY PWR
FRONT CONNECTOR
BACK CONNECTOR

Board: 2 copper layers, 86 parts (1 on the bottom side), 104 nets, no tracks yet.

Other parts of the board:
U$7: ADAFRUIT_3.5MM
